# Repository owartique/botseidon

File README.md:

# botseidon
LELME2002 - Project Mechatronics

Before making a mess on this repository, please get familiar with github. 

Here are some useful links:
* GitHub tutorial : https://guides.github.com/activities/hello-world/
* OpenClassRoom course : https://openclassrooms.com/fr/courses/5641721-utilisez-git-et-github-pour-vos-projets-de-developpement
* YouTube : https://www.youtube.com/watch?v=nhNq2kIvi9s&ab_channel=freeCodeCamp.org
* GitHub documentation : https://docs.github.com/en
* Many more ...

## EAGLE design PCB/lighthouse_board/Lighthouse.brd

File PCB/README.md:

# PCB

Always include the .sch and .brd files in the same directory

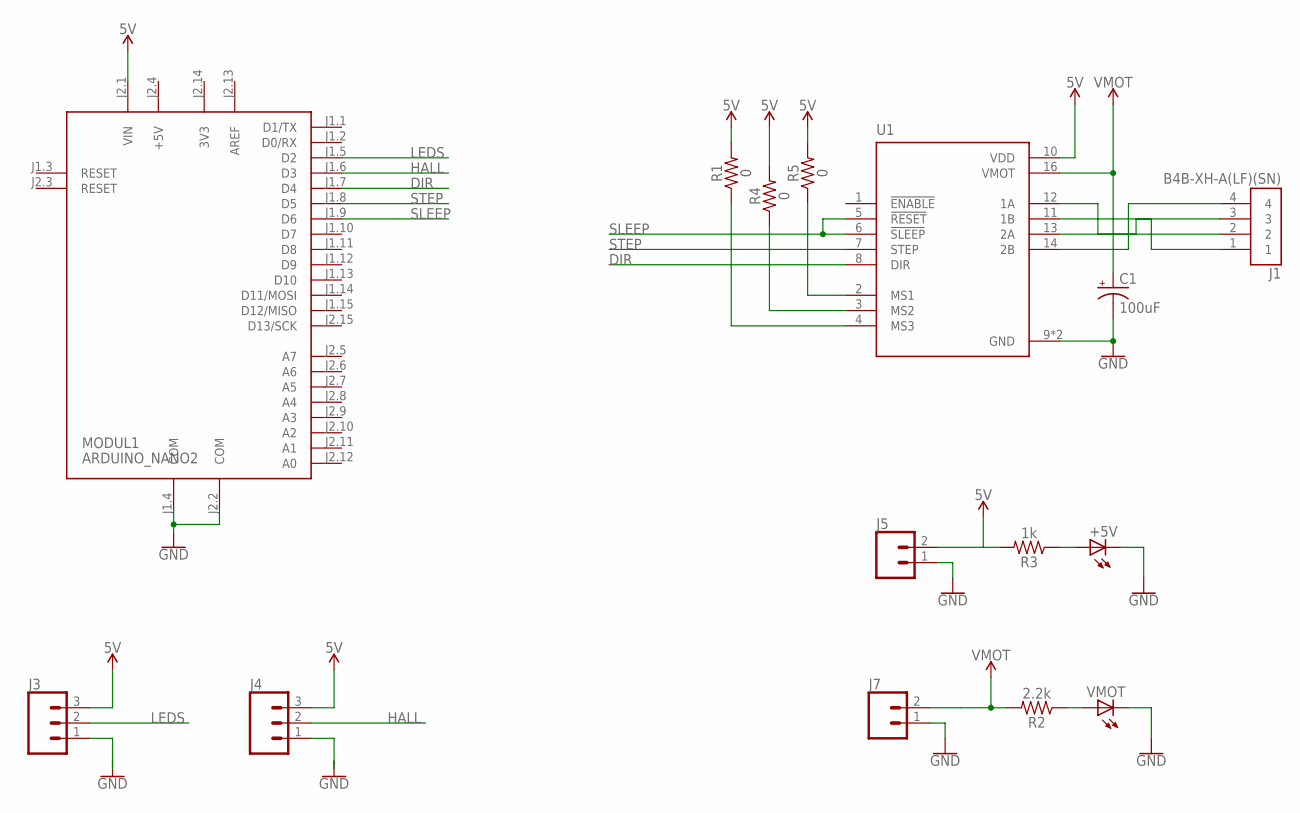
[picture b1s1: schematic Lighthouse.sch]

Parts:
+5V: LEDP-LCC-2; P-LCC-2
C1: 100uF; PANASONIC_D
J1: B4B-XH-A(LF)(SN); JST_B4B-XH-A(LF)(SN)
J3, J4: CONN_03SCREW; SCREWTERMINAL-3.5MM-3
J5, J7: CONN_025MM; SCREWTERMINAL-5MM-2
MODUL1: ARDUINO_NANO2
R1, R4, R5: 0; 1206
R2: 2.2k; 1206
R3: 1k; 1206
U1: A4988_STEPPER_MOTOR_DRIVER_CARRIER; MODULE_A4988_STEPPER_MOTOR_DRIVER_CARRIER
VMOT: LEDP-LCC-2; P-LCC-2

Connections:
3V3: MODUL1.J2.14 (3V3)
5V: J3.3, J4.3, J5.2, MODUL1.J2.1 (VIN), R1.2, R3.2, R4.2, R5.2, U1.10 (VDD)
12V: C1.+, J7.2, R2.2, U1.16 (VMOT)
+5V: MODUL1.J2.4 (+5V)
AREF: MODUL1.J2.13 (AREF)
DIR: MODUL1.J1.7 (D4), U1.8 (DIR)
GND: +5V.C, C1.-, J3.1, J4.1, J5.1, J7.1, MODUL1.J1.4 (COM), MODUL1.J2.2 (COM), U1.9 (GND), U1.15 (GND), VMOT.C
HALL: J4.2, MODUL1.J1.6 (D3)
LEDS: J3.2, MODUL1.J1.5 (D2)
unnamed: +5V.A, R3.1
unnamed: R2.1, VMOT.A
unnamed: J1.4, U1.14 (2B)
unnamed: J1.3, U1.13 (2A)
unnamed: J1.1, U1.11 (1B)
unnamed: J1.2, U1.12 (1A)
unnamed: R1.1, U1.4 (MS3)
unnamed: R4.1, U1.3 (MS2)
unnamed: R5.1, U1.2 (MS1)
SLEEP: MODUL1.J1.9 (D6), U1.5 (!RESET), U1.6 (!SLEEP)
STEP: MODUL1.J1.8 (D5), U1.7 (STEP)

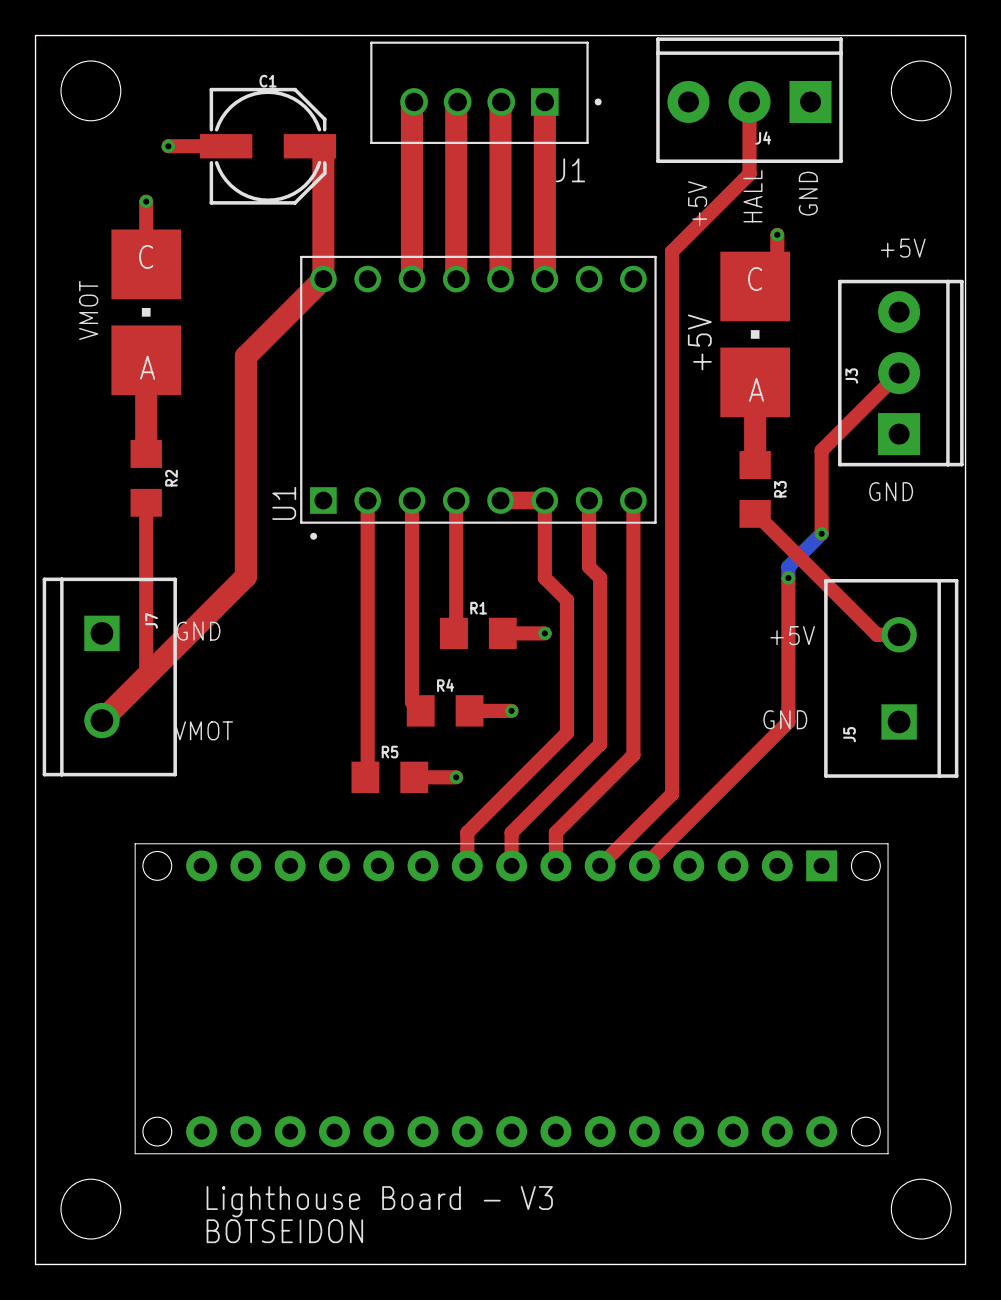
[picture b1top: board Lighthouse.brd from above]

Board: 2 copper layers, 53.3 x 70.5 mm, 15 parts (0 on the bottom side), 17 nets.

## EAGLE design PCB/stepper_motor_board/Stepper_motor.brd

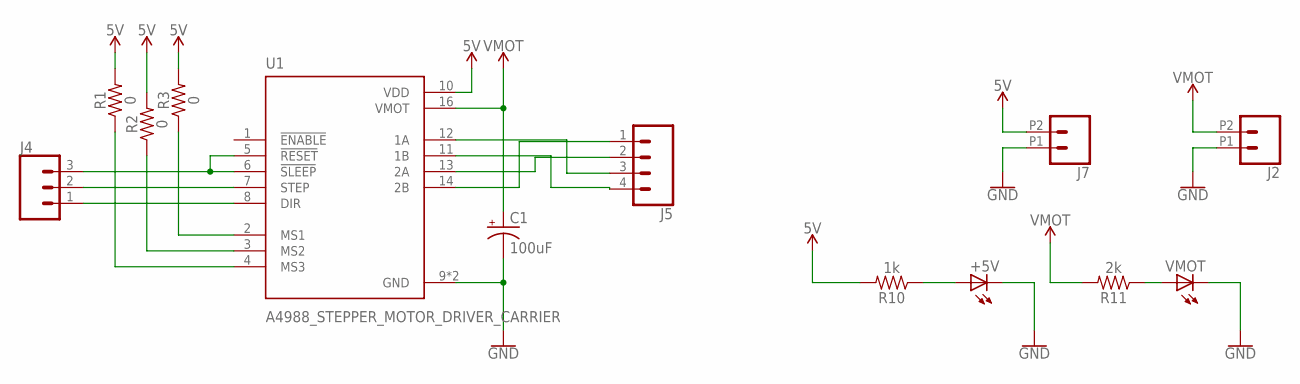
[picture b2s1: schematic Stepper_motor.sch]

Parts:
+5V: LEDP-LCC-2; P-LCC-2
C1: 100uF; PANASONIC_D
J2, J7: CONN_02SCREWTERMINAL-6.35MM-2; 1X02_6.35_SCREWTERM
J4: CONN_03SCREW; SCREWTERMINAL-3.5MM-3
J5: CONN_04JST-PTH-VERT; JST-4-PTH-VERT
R1, R2, R3: 0; 1206
R10: 1k; 1206
R11: 2k; 1206
U1: A4988_STEPPER_MOTOR_DRIVER_CARRIER; MODULE_A4988_STEPPER_MOTOR_DRIVER_CARRIER
VMOT: LEDP-LCC-2; P-LCC-2

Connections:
5V: J7.P2 (1), R1.2, R2.2, R3.2, R10.2, U1.10 (VDD)
12V: C1.+, J2.P2 (1), R11.2, U1.16 (VMOT)
GND: +5V.C, C1.-, J2.P1 (2), J7.P1 (2), U1.9 (GND), U1.15 (GND), VMOT.C
unnamed: J5.4, U1.11 (1B)
unnamed: J5.3, U1.12 (1A)
unnamed: J5.2, U1.13 (2A)
unnamed: J5.1, U1.14 (2B)
unnamed: J4.2, U1.7 (STEP)
unnamed: J4.1, U1.8 (DIR)
unnamed: J4.3, U1.5 (!RESET), U1.6 (!SLEEP)
unnamed: R3.1, U1.2 (MS1)
unnamed: R2.1, U1.3 (MS2)
unnamed: R1.1, U1.4 (MS3)
unnamed: +5V.A, R10.1
unnamed: R11.1, VMOT.A

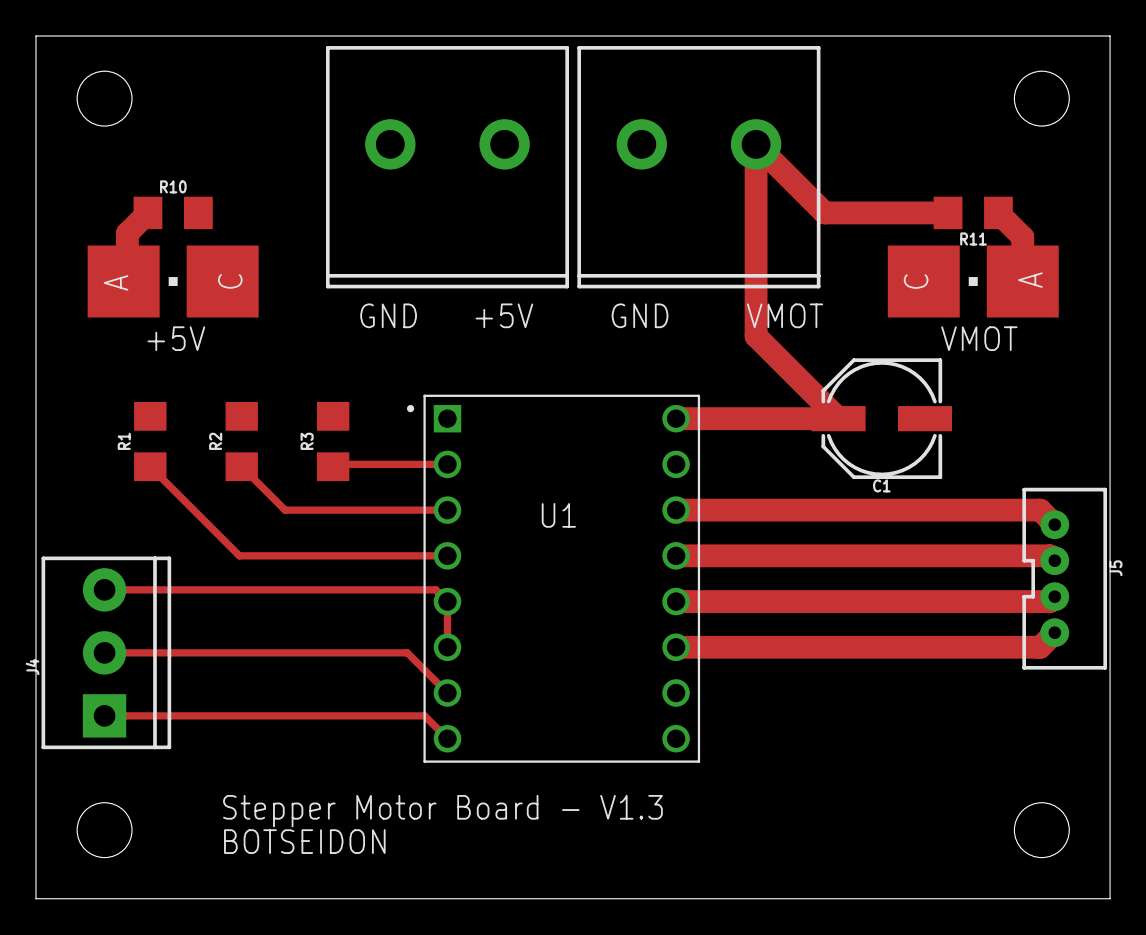
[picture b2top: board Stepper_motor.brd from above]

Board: 2 copper layers, 59.7 x 47.9 mm, 13 parts (0 on the bottom side), 15 nets.

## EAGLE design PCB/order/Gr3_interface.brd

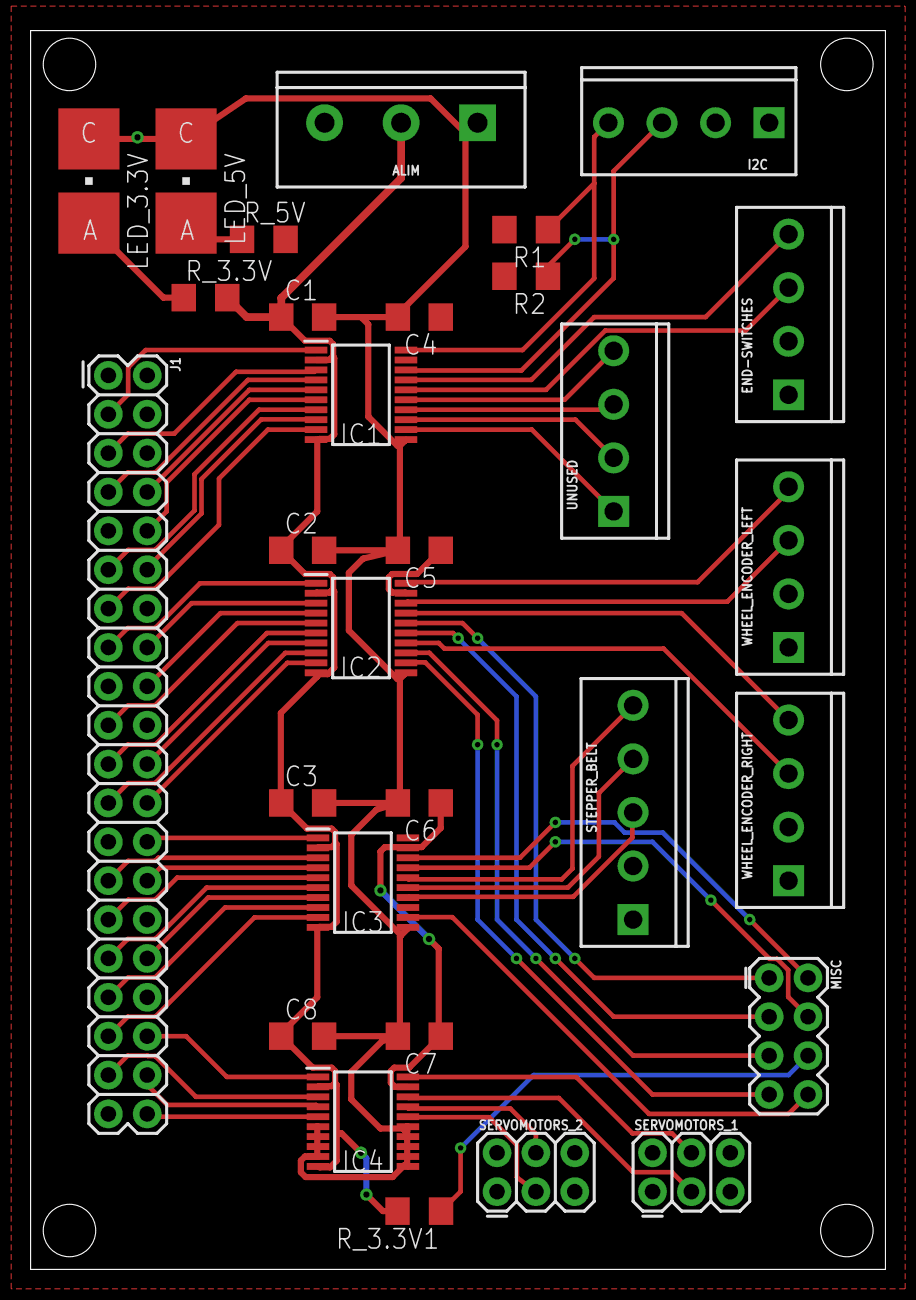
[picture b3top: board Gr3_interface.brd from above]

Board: 2 copper layers, 55.9 x 81.0 mm, 30 parts (0 on the bottom side), 60 nets.

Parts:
ALIM: SCREWTERMINAL-5MM-3
C1, C2, C3, C4, C5, C6, C7, C8: 0.1uF; C1206
END-SWITCHES: SCREWTERMINAL-3.5MM-4
I2C: SCREWTERMINAL-3.5MM-4
IC1, IC2, IC3, IC4: TXS0108EPWR; SOP65P640X120-20N
J1: RASPBERRYPI-40-PIN-GPIO_PTH_NO_SHROUD; 2X20
LED_3.3V, LED_5V: GREEN; P-LCC-2
MISC: 2X4
R1, R2: 10k; R1206
R_3.3V, R_3.3V1, R_5V: 1k; R1206
SERVOMOTORS_1, SERVOMOTORS_2: 2X3
STEPPER_BELT: SCREWTERMINAL-3.5MM-5
UNUSED: SCREWTERMINAL-3.5MM-4
WHEEL_ENCODER_LEFT: SCREWTERMINAL-3.5MM-4
WHEEL_ENCODER_RIGHT: SCREWTERMINAL-3.5MM-4

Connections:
3.3V: ALIM.2, C1.1, C2.1, C3.1, C8.1, IC1.2, IC1.10, IC2.2, IC2.10, IC3.2, IC3.10, IC4.2, IC4.10, R_3.3V.2, R_3.3V1.2
5V: ALIM.3, C4.1, C5.1, C6.1, C7.1, END-SWITCHES.2, I2C.2, IC1.19, IC2.19, IC3.19, IC4.19, R1.2, R2.2, R_5V.2, SERVOMOTORS_1.1, SERVOMOTORS_1.2, SERVOMOTORS_2.1, SERVOMOTORS_2.2, STEPPER_BELT.2, WHEEL_ENCODER_LEFT.2, WHEEL_ENCODER_RIGHT.2
BELT_DIR: IC3.14, STEPPER_BELT.3
BELT_ENABLE: IC3.16, STEPPER_BELT.5
BELT_STEP: IC3.15, STEPPER_BELT.4
CE0: IC2.9, J1.24
CE0-5V: IC2.12, MISC.7
CE1: IC3.1, J1.26
END-SWITCH_1: END-SWITCHES.4, IC1.17
END-SWITCH_2: END-SWITCHES.3, IC1.16
GND: ALIM.1, C1.2, C2.2, C3.2, C4.2, C5.2, C6.2, C7.2, C8.2, END-SWITCHES.1, I2C.1, IC1.11, IC2.11, IC3.11, IC4.6, IC4.7, IC4.8, IC4.9, IC4.11, IC4.12, IC4.13, IC4.14, IC4.15, J1.6, J1.9, J1.14, J1.20, J1.25, J1.30, J1.34, J1.39, LED_3.3V.C, LED_5V.C, SERVOMOTORS_1.5, SERVOMOTORS_1.6, SERVOMOTORS_2.5, SERVOMOTORS_2.6, STEPPER_BELT.1, WHEEL_ENCODER_LEFT.1, WHEEL_ENCODER_RIGHT.1
GP4: IC1.4, J1.7
GP5: IC3.5, J1.29
GP6: IC3.6, J1.31
GP12: IC3.7, J1.32
GP13: IC3.8, J1.33
GP16: IC4.1, J1.36
GP17: IC1.7, J1.11
GP18: IC1.8, J1.12
GP19: IC3.9, J1.35
GP20: IC4.4, J1.38
GP21: IC4.5, J1.40
GP22: IC2.1, J1.15
GP23: IC2.3, J1.16
GP24: IC2.4, J1.18
GP25: IC2.7, J1.22
GP26: IC4.3, J1.37
GP27: IC1.9, J1.13
ID_SC: IC3.4, J1.28
ID_SC-5V: IC3.17, MISC.4
ID_SD: IC3.3, J1.27
ID_SD-5V: IC3.18, MISC.2
INFRARED_SENSING: IC3.12, MISC.8
INFRARED_SUPPLY: MISC.6, R_3.3V1.1
MISO: IC2.6, J1.21
MISO-5V: IC2.15, MISC.3
MOSI: IC2.5, J1.19
MOSI-5V: IC2.16, MISC.1
unnamed: LED_3.3V.A, R_3.3V.1
unnamed: LED_5V.A, R_5V.1
RXI: IC1.6, J1.10
SCL: IC1.3, J1.5
SCL-5V: I2C.3, IC1.18, R2.1
SCLK: IC2.8, J1.23
SCLK-5V: IC2.13, MISC.5
SDA: IC1.1, J1.3
SDA-5V: I2C.4, IC1.20, R1.1
SERVO_BACK: IC4.20, SERVOMOTORS_1.4
SERVO_CLAMP: IC4.17, SERVOMOTORS_2.4
SERVO_FLAG: IC4.16, SERVOMOTORS_2.3
SERVO_RACK: IC4.18, SERVOMOTORS_1.3
TXO: IC1.5, J1.8
UNUSED_1: IC1.15, UNUSED.4
UNUSED_2: IC1.14, UNUSED.3
UNUSED_3: IC1.13, UNUSED.2
UNUSED_4: IC1.12, UNUSED.1
W_LEFT_A: IC2.20, WHEEL_ENCODER_LEFT.4
W_LEFT_B: IC2.18, WHEEL_ENCODER_LEFT.3
W_RIGHT_A: IC2.17, WHEEL_ENCODER_RIGHT.4
W_RIGHT_B: IC2.14, WHEEL_ENCODER_RIGHT.3

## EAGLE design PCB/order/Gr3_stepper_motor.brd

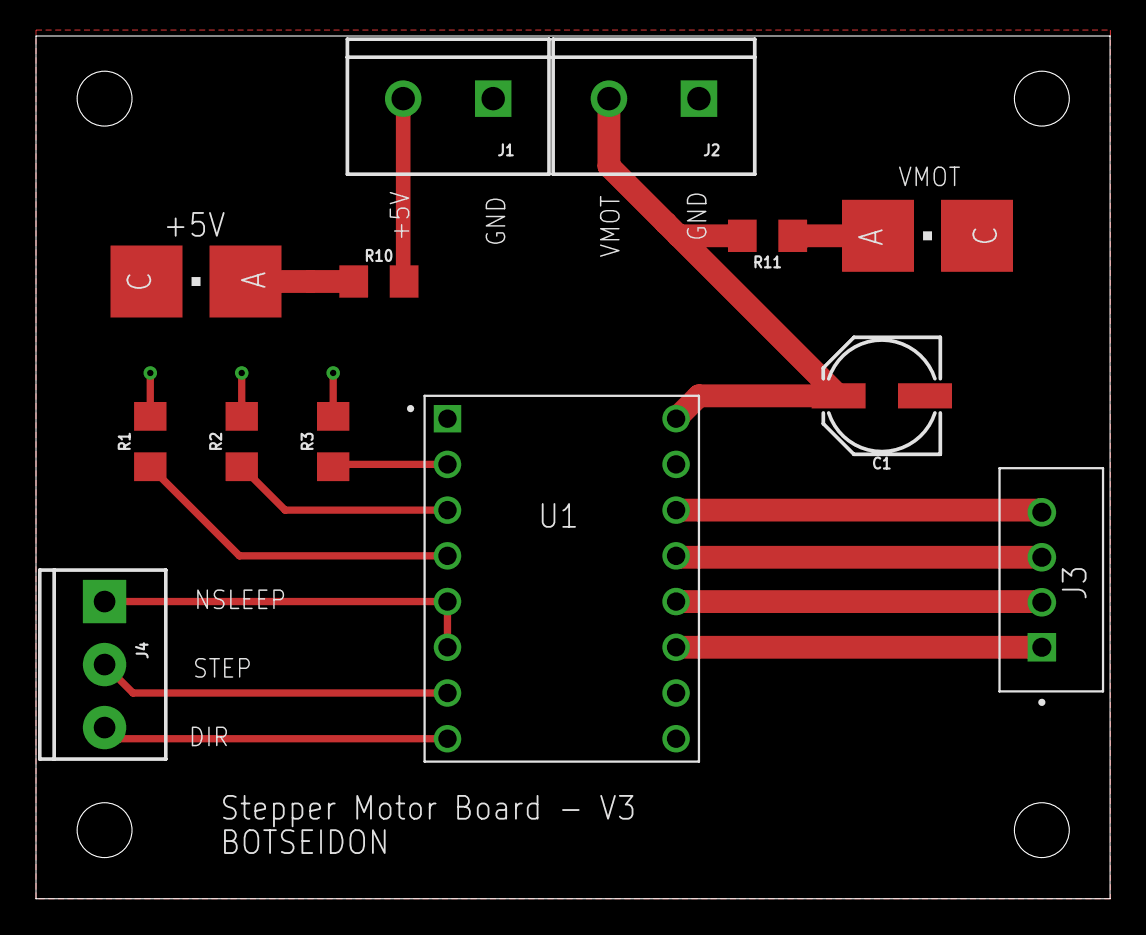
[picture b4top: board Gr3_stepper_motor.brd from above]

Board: 2 copper layers, 59.7 x 47.9 mm, 13 parts (0 on the bottom side), 15 nets.

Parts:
+5V: P-LCC-2
C1: 100uF; PANASONIC_D
J1, J2: SCREWTERMINAL-5MM-2
J3: B4B-XH-A(LF)(SN); JST_B4B-XH-A(LF)(SN)
J4: SCREWTERMINAL-3.5MM-3
R1, R2, R3: 0; 1206
R10: 1k; 1206
R11: 2k; 1206
U1: A4988_STEPPER_MOTOR_DRIVER_CARRIER; MODULE_A4988_STEPPER_MOTOR_DRIVER_CARRIER
VMOT: P-LCC-2

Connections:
5V: J1.2, R1.2, R2.2, R3.2, R10.2, U1.10
12V: C1.+, J2.2, R11.2, U1.16
GND: +5V.C, C1.-, J1.1, J2.1, U1.9, U1.15, VMOT.C
unnamed: J3.1, U1.11
unnamed: J3.2, U1.12
unnamed: J3.3, U1.13
unnamed: J3.4, U1.14
unnamed: J4.2, U1.7
unnamed: J4.3, U1.8
unnamed: J4.1, U1.5, U1.6
unnamed: R3.1, U1.2
unnamed: R2.1, U1.3
unnamed: R1.1, U1.4
unnamed: +5V.A, R10.1
unnamed: R11.1, VMOT.A

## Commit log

2020-11-23 remove typo
2020-11-23 add youtube resource
2020-11-23 added .sch and .brd files
2020-11-23 removed file
2020-11-23 removed .sch file
2020-11-23 added pcb directory with readme
2020-11-23 added the files for the stepper motor board
2020-11-23 added lighthouse board files
2020-11-23 added github docu
2020-11-23 added GrayCode_C files in Minibot directory
2020-11-23 rearranging files
2020-11-23 added GrayCode_C files
2020-11-23 added WhiteSpirit_python files
2020-11-23 added github tuto
2020-11-23 added pseudo_code.c
2020-11-23 added useful ressources
2020-11-23 typo
2020-11-23 updated to do list in readme
2020-11-24 added main.c code
2020-11-24 updated readme and added main.c instead of main
2020-11-24 new udpate of main.cc after reading rplidar docu
2020-11-24 added variable op_result
2020-11-24 declaration variable quality
2020-11-24 correction compil
2020-11-24 compil
2020-11-24 correction type obstacle
2020-11-24 corrected a few mistakes
2020-11-24 corrected quality factor
2020-11-24 print debugging
2020-11-24 small update
2020-11-25 changed type of dist from int to float
2020-11-25 new functions
2020-11-25 modif indentation
2020-11-25 minibot is following us!!!
2020-11-25 update function whereIsBeacon() now the minibot will follow the closest object
2020-11-25 Ajout controller cc et hh (ils compilent)
2020-11-25 added a copy of the files of the minibot and updated readme
2020-11-25 added slamware directory
2020-11-26 update functions
2020-11-28 added sv files
2020-11-28 deleted main file
2020-11-28 module decode
2020-11-28 minibot will now detect object 360 around instead of 180 in front
2020-11-29 udpate sv file
2020-11-30 clock divider
2020-12-02 added python script
2020-12-03 quelques modifs pour la vitesse
2020-12-04 cleaning du code (variables, commentaires etc)
2020-12-04 cleaned everything, see readme for more info
2020-12-04 new version of stepper pcb and lighthouse pcb
2020-12-05 cleaning
2020-12-06 gros update avec le controller
2021-01-23 new files
2021-02-03 update pcb for order
2021-02-03 update pcb order interface
2021-03-19 added comm and cam files
2021-03-19 added com and cam files
2021-03-20 added original camera files
2021-03-20 cam succesfully detect N and S

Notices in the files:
parts and their libraries:
SparkFun-Capacitors: Licensing: Creative Commons ShareAlike 4.0 International - https://creativecommons.org/licenses/by-sa/4.0
